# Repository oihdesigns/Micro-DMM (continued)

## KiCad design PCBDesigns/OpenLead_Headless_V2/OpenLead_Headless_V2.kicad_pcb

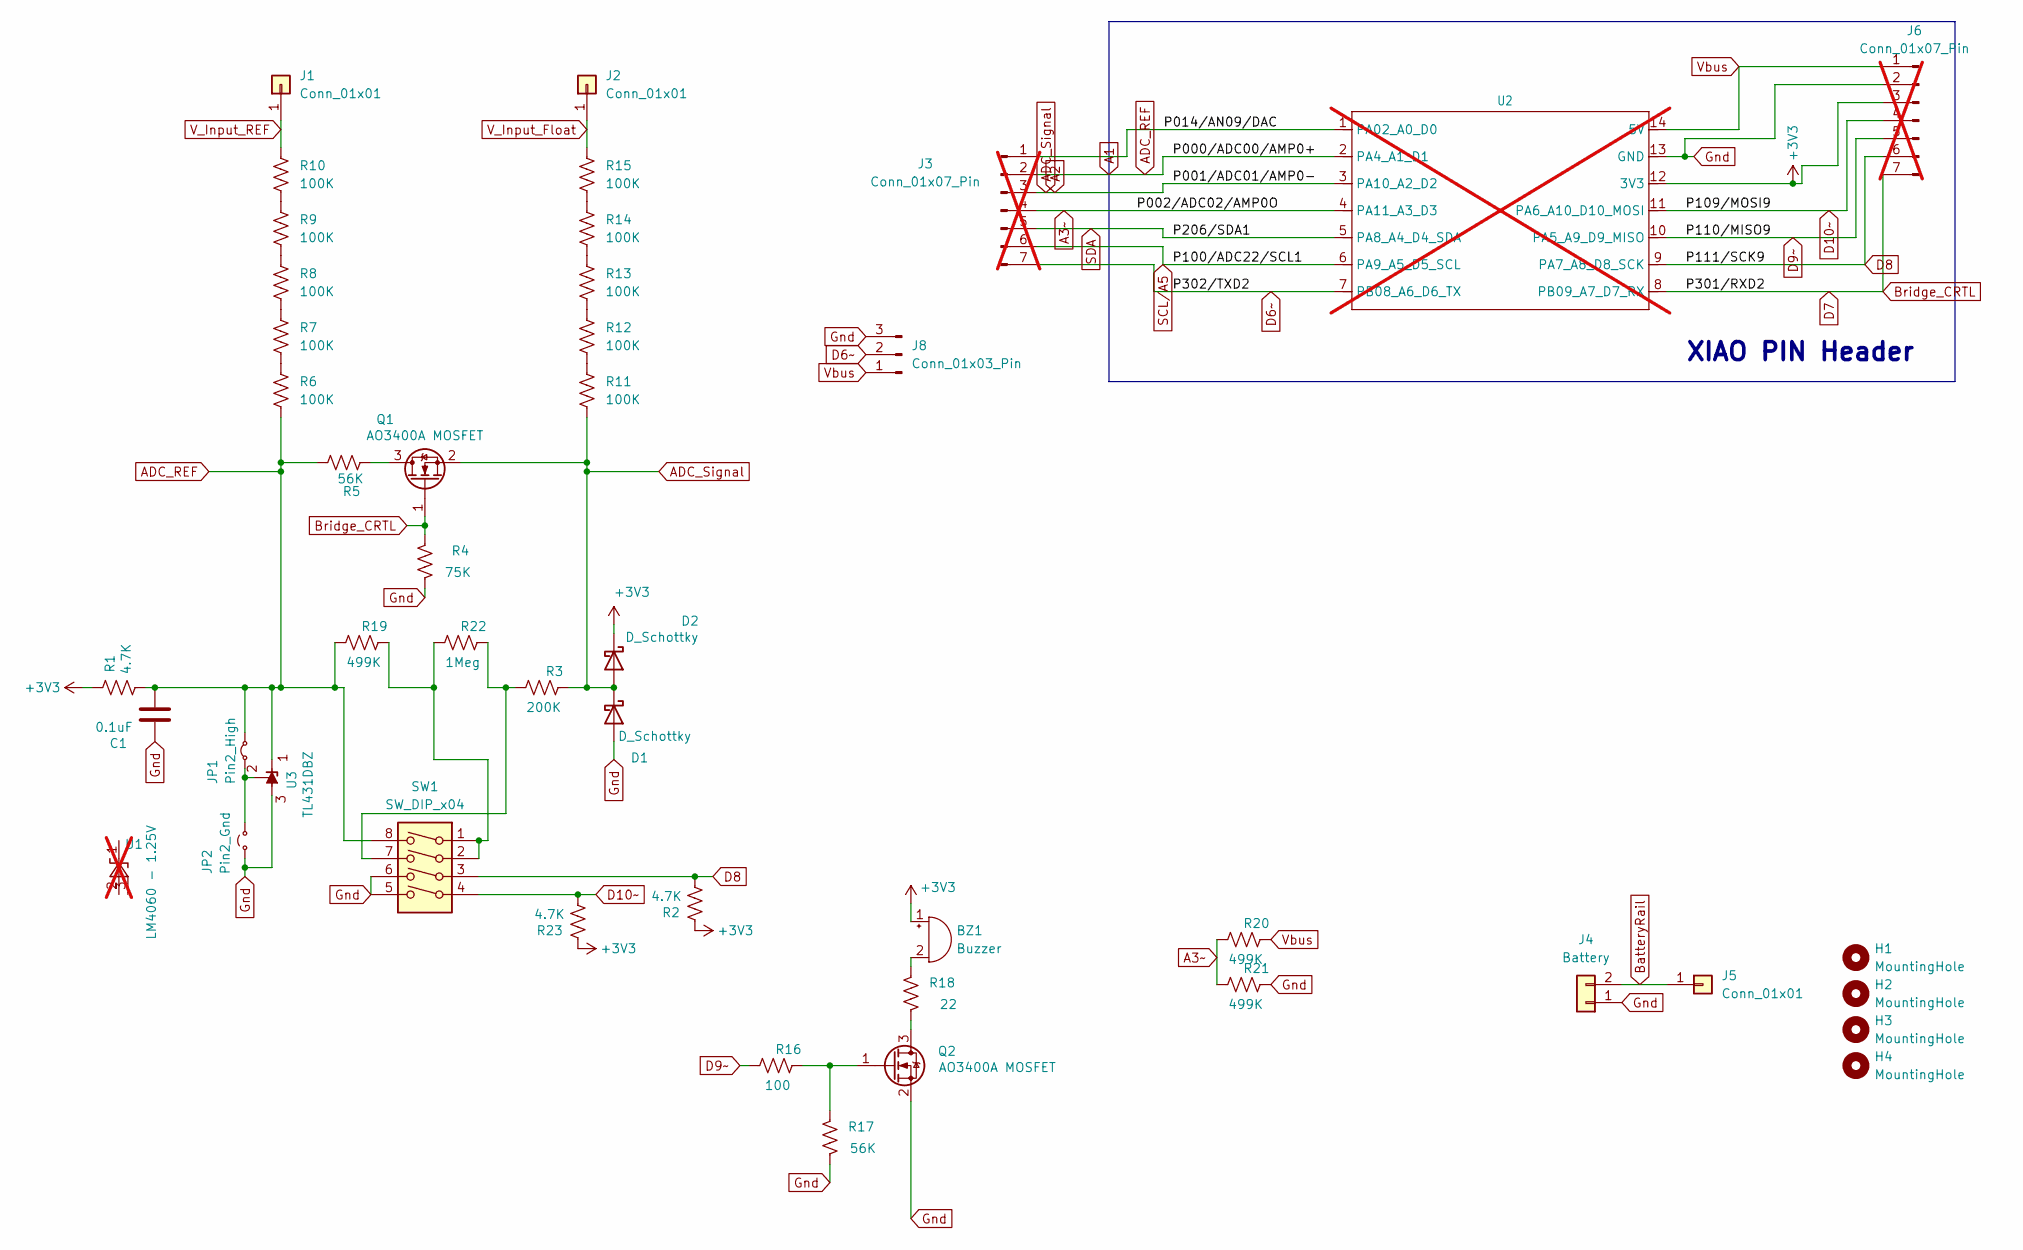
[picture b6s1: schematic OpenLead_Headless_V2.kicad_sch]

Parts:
BZ1: Buzzer; Buzzer_12x9.5RM7.6
C1: 0.1uF; C_0805_2012Metric
D1, D2: D_Schottky; D_SOD-123
H1, H2, H3, H4: MountingHole; MountingHole_2.2mm_M2_Pad
J1, J2: Conn_01x01; SolderWire-0.75sqmm_1x01_D1.25mm_OD2.3mm
J3, J6: Conn_01x07_Pin; PinSocket_1x07_P2.54mm_Vertical; not fitted
J4: Battery; PinHeader_1x02_P1.27mm_Vertical
J5: Conn_01x01; SolderWire-0.5sqmm_1x01_D0.9mm_OD2.1mm
J8: Conn_01x03_Pin; PinHeader_1x03_P1.27mm_Vertical
JP1: Pin2_High; SolderJumper-2_P1.3mm_Bridged_Pad1.0x1.5mm
JP2: Pin2_Gnd; SolderJumper-2_P1.3mm_Open_TrianglePad1.0x1.5mm
Q1, Q2: AO3400A MOSFET; SOT-23
R1, R2, R23: 4.7K; R_0805_2012Metric
R3: 200K; R_0805_2012Metric
R4: 75K; R_0805_2012Metric
R5, R17: 56K; R_0805_2012Metric
R6, R7, R8, R9, R10, R11, R12, R13, R14, R15: 100K; R_0805_2012Metric
R16: 100; R_0805_2012Metric
R18: 22; R_0805_2012Metric
R19, R20, R21: 499K; R_0805_2012Metric
R22: 1Meg; R_0805_2012Metric
SW1: SW_DIP_x04; SW_DIP_SPSTx04_Slide_KingTek_DSHP04TS_W7.62mm_P1.27mm
U1: LM4060 - 1.25V; SOT-23; not fitted
U2: not fitted
U3: TL431DBZ; SOT-23

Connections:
+3V3: BZ1.1 (+), D2.1 (K), J6.3, R1.1, R2.1, R23.1, U2.12 (3V3)
/P014/AN09/DAC: J3.1, U2.1 (PA02_A0_D0)
A1: C1.2, J3.2, JP1.2 (B), R1.2, R5.2, R6.2, R19.1, SW1.8, U2.2 (PA4_A1_D1), U3.1 (K)
A2: D1.1 (K), D2.2 (A), J3.3, Q1.2 (S), R3.2, R11.2, U2.3 (PA10_A2_D2)
A3~: J3.4, R20.1, R21.1, U2.4 (PA11_A3_D3)
BatteryRail: J4.2, J5.1 (Pin_1_1)
Bridge_CRTL: J6.7, Q1.1 (G), R4.2, U2.8 (PB09_A7_D7_RX)
D6~: J3.7, J8.2, U2.7 (PB08_A6_D6_TX)
D8: J6.6, R2.2, SW1.3, U2.9 (PA7_A8_D8_SCK)
D9~: J6.5, R16.1, U2.10 (PA5_A9_D9_MISO)
D10~: J6.4, R23.2, SW1.4, U2.11 (PA6_A10_D10_MOSI)
Gnd: C1.1, D1.2 (A), J4.1, J6.2, J8.3, JP2.1 (A), Q2.2 (S), R4.1, R17.1, R21.2, SW1.5, SW1.6, U2.13 (GND), U3.3 (A)
unnamed: BZ1.2 (-), R18.2
unnamed: JP1.1 (A), JP2.2 (B), U3.2 (REF)
unnamed: Q1.3 (D), R5.1
unnamed: Q2.3 (D), R18.1
unnamed: Q2.1 (G), R16.2, R17.2
unnamed: R6.1, R7.2
unnamed: R7.1, R8.2
unnamed: R8.1, R9.2
unnamed: R9.1, R10.2
unnamed: R11.1, R12.2
unnamed: R12.1, R13.2
unnamed: R13.1, R14.2
unnamed: R14.1, R15.2
unnamed: R19.2, R22.1, SW1.1, SW1.2
unnamed: R3.1, R22.2, SW1.7
SCL/A5: J3.6, U2.6 (PA9_A5_D5_SCL)
SDA: J3.5, U2.5 (PA8_A4_D4_SDA)
V_Input_Float: J2.1 (Pin_1_1), R15.1
V_Input_REF: J1.1 (Pin_1_1), R10.1
Vbus: J6.1, J8.1, R20.2, U2.14 (5V)

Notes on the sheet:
XIAO PIN Header

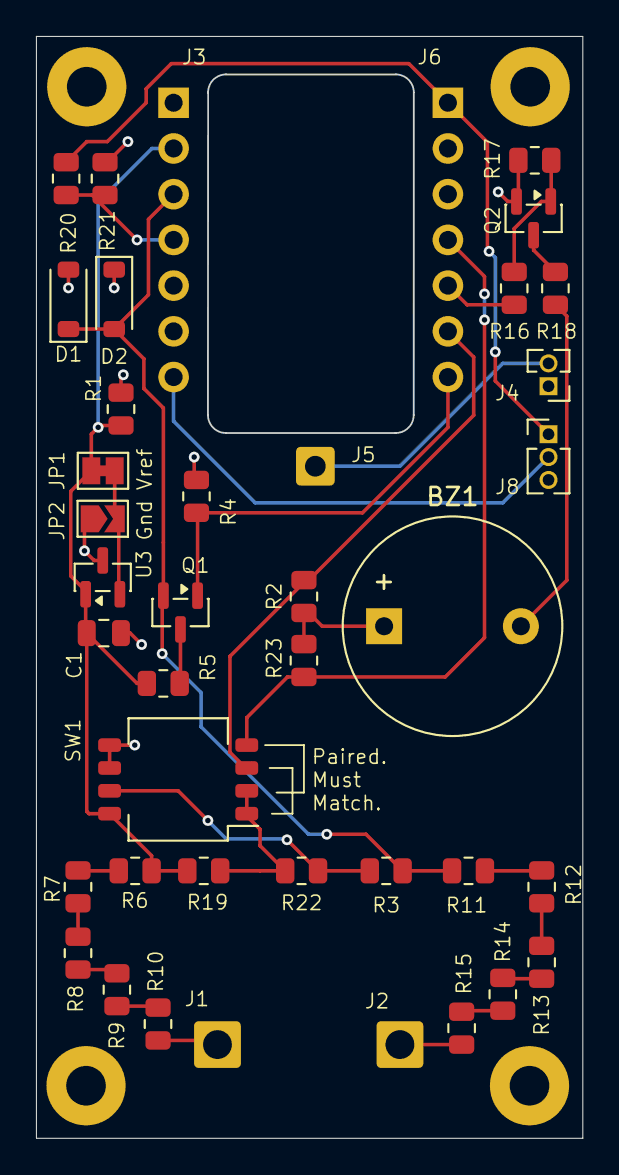
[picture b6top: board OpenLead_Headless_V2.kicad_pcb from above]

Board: 4 copper layers, 30.4 x 61.2 mm, 44 parts (0 on the bottom side), 29 nets.

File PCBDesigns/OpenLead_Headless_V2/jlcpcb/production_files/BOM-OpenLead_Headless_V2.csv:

Comment,Designator,Footprint,LCSC,Quantity
0.1uF,C1,C_0805_2012Metric,C28233,1
100,R16,R_0805_2012Metric,C17408,1
100K,"R10,R11,R12,R13,R14,R15,R6,R7,R8,R9",R_0805_2012Metric,C122537,10
1Meg,R22,R_0805_2012Metric,C445668,1
200K,R3,R_0805_2012Metric,C218415,1
22,R18,R_0805_2012Metric,C17561,1
4.7K,"R1,R2,R23",R_0805_2012Metric,C515732,3
499K,"R19,R20,R21",R_0805_2012Metric,C218596,3
56K,"R17,R5",R_0805_2012Metric,C218627,2
75K,R4,R_0805_2012Metric,C319485,1
AO3400A MOSFET,"Q1,Q2",SOT-23,C20917,2
D_Schottky,"D1,D2",D_SOD-123,C8598,2
SW_DIP_x04,SW1,SW_DIP_SPSTx04_Slide_KingTek_DSHP04TS_W7.62mm_P1.27mm,C3293144,1
TL431DBZ,U3,SOT-23,C8499,1
Conn_01x01,J1,SolderWire-0.75sqmm_1x01_D1.25mm_OD2.3mm,,1
Battery,J4,PinHeader_1x02_P1.27mm_Vertical,,1
Conn_01x01,J5,SolderWire-0.5sqmm_1x01_D0.9mm_OD2.1mm,,1
Conn_01x01,J2,SolderWire-0.75sqmm_1x01_D1.25mm_OD2.3mm,,1
Buzzer,BZ1,Buzzer_12x9.5RM7.6,,1
Conn_01x03_Pin,J8,PinHeader_1x03_P1.27mm_Vertical,,1
Pin2_Gnd,JP2,SolderJumper-2_P1.3mm_Open_TrianglePad1.0x1.5mm,,1
Pin2_High,JP1,SolderJumper-2_P1.3mm_Bridged_Pad1.0x1.5mm,,1

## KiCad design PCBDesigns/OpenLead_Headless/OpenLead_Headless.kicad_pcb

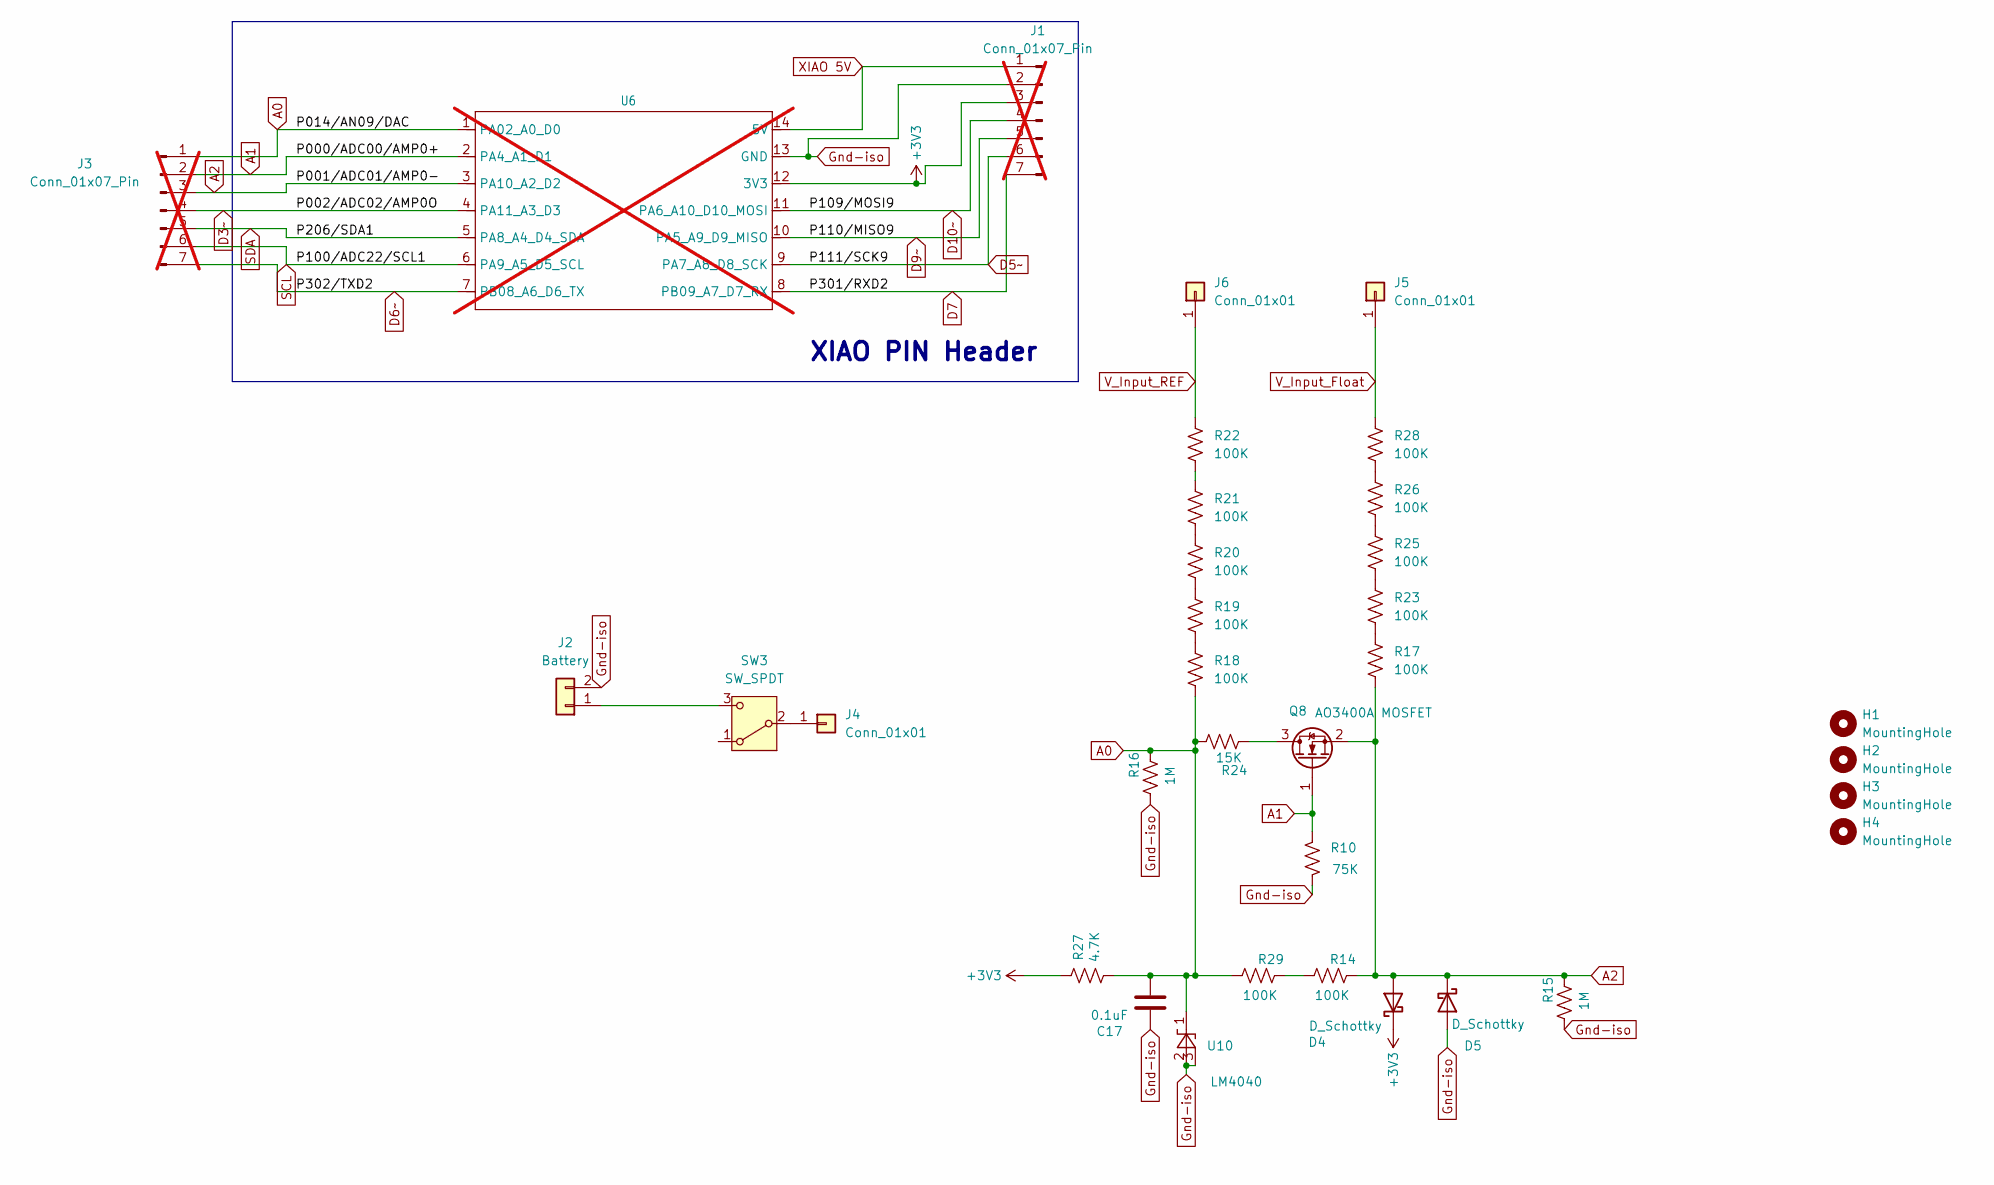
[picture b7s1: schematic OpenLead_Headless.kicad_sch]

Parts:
C17: 0.1uF; C_0805_2012Metric
D4, D5: D_Schottky; D_SOD-123
H1, H2, H3, H4: MountingHole; MountingHole_2.2mm_M2_Pad
J1, J3: Conn_01x07_Pin; PinSocket_1x07_P2.54mm_Vertical; not fitted
J2: Battery; PinSocket_1x02_P2.54mm_Vertical
J4: Conn_01x01; SolderWire-0.5sqmm_1x01_D0.9mm_OD2.1mm
J5, J6: Conn_01x01; SolderWire-0.75sqmm_1x01_D1.25mm_OD2.3mm
Q8: AO3400A MOSFET; SOT-23
R10: 75K; R_0805_2012Metric
R14, R17, R18, R19, R20, R21, R22, R23, R25, R26, R28, R29: 100K; R_0805_2012Metric
R15, R16: 1M; R_0805_2012Metric
R24: 15K; R_0805_2012Metric
R27: 4.7K; R_0805_2012Metric
SW3: SW_SPDT; SW_Slide_SPDT_Angled_CK_OS102011MA1Q
U6: not fitted
U10: LM4040; SOT-23

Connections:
+3V3: D4.1 (K), J1.3, R27.1, U6.12 (3V3)
A0: C17.2, J3.1, R16.2, R18.2, R24.2, R27.2, R29.1, U6.1 (PA02_A0_D0), U10.1 (K)
A1: J3.2, Q8.1 (G), R10.2, U6.2 (PA4_A1_D1)
A2: D4.2 (A), D5.1 (K), J3.3, Q8.2 (S), R14.2, R15.2, R17.2, U6.3 (PA10_A2_D2)
D3~: J3.4, U6.4 (PA11_A3_D3)
D5~: J1.6, U6.9 (PA7_A8_D8_SCK)
D6~: J3.7, U6.7 (PB08_A6_D6_TX)
D7: J1.7, U6.8 (PB09_A7_D7_RX)
D9~: J1.5, U6.10 (PA5_A9_D9_MISO)
D10~: J1.4, U6.11 (PA6_A10_D10_MOSI)
Gnd-iso: C17.1, D5.2 (A), J1.2, J2.2, R10.1, R15.1, R16.1, U6.13 (GND), U10.2 (A), U10.3 (nc_(gnd))
unnamed: J2.1, SW3.3 (C)
unnamed: J4.1 (Pin_1_1), SW3.2 (B)
unnamed: Q8.3 (D), R24.1
unnamed: R14.1, R29.2
unnamed: R17.1, R23.2
unnamed: R18.1, R19.2
unnamed: R19.1, R20.2
unnamed: R20.1, R21.2
unnamed: R21.1, R22.2
unnamed: R23.1, R25.2
unnamed: R25.1, R26.2
unnamed: R26.1, R28.2
SCL: J3.6, U6.6 (PA9_A5_D5_SCL)
SDA: J3.5, U6.5 (PA8_A4_D4_SDA)
V_Input_Float: J5.1 (Pin_1_1), R28.1
V_Input_REF: J6.1 (Pin_1_1), R22.1
XIAO 5V: J1.1, U6.14 (5V)

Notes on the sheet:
XIAO PIN Header

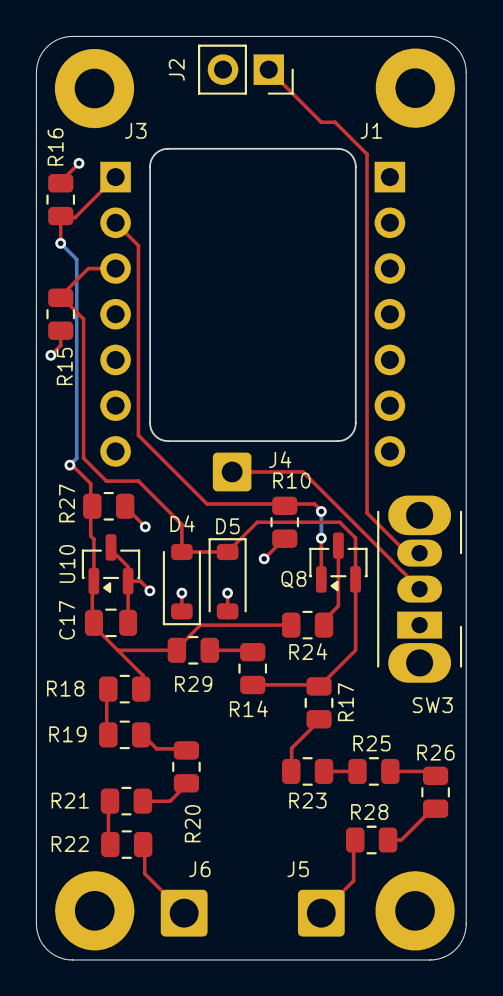
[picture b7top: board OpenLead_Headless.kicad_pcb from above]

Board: 4 copper layers, 23.9 x 51.3 mm, 33 parts (0 on the bottom side), 19 nets.

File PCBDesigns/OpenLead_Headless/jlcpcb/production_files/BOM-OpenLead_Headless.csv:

Comment,Designator,Footprint,LCSC,Quantity
0.1uF,C17,C_0805_2012Metric,C28233,1
100K,"R14,R17,R18,R19,R20,R21,R22,R23,R25,R26,R28,R29",R_0805_2012Metric,C122537,12
15K,R24,R_0805_2012Metric,C319846,1
1M,"R15,R16",R_0805_2012Metric,C218408,2
4.7K,R27,R_0805_2012Metric,C515732,1
75K,R10,R_0805_2012Metric,C319485,1
AO3400A MOSFET,Q8,SOT-23,C20917,1
D_Schottky,"D4,D5",D_SOD-123,C8598,2
LM4040,U10,SOT-23,C2156621,1
Conn_01x01,J4,SolderWire-0.5sqmm_1x01_D0.9mm_OD2.1mm,,1
Conn_01x01,J6,SolderWire-0.75sqmm_1x01_D1.25mm_OD2.3mm,,1
Conn_01x01,J5,SolderWire-0.75sqmm_1x01_D1.25mm_OD2.3mm,,1
Battery,J2,PinSocket_1x02_P2.54mm_Vertical,,1
SW_SPDT,SW3,SW_Slide_SPDT_Angled_CK_OS102011MA1Q,,1

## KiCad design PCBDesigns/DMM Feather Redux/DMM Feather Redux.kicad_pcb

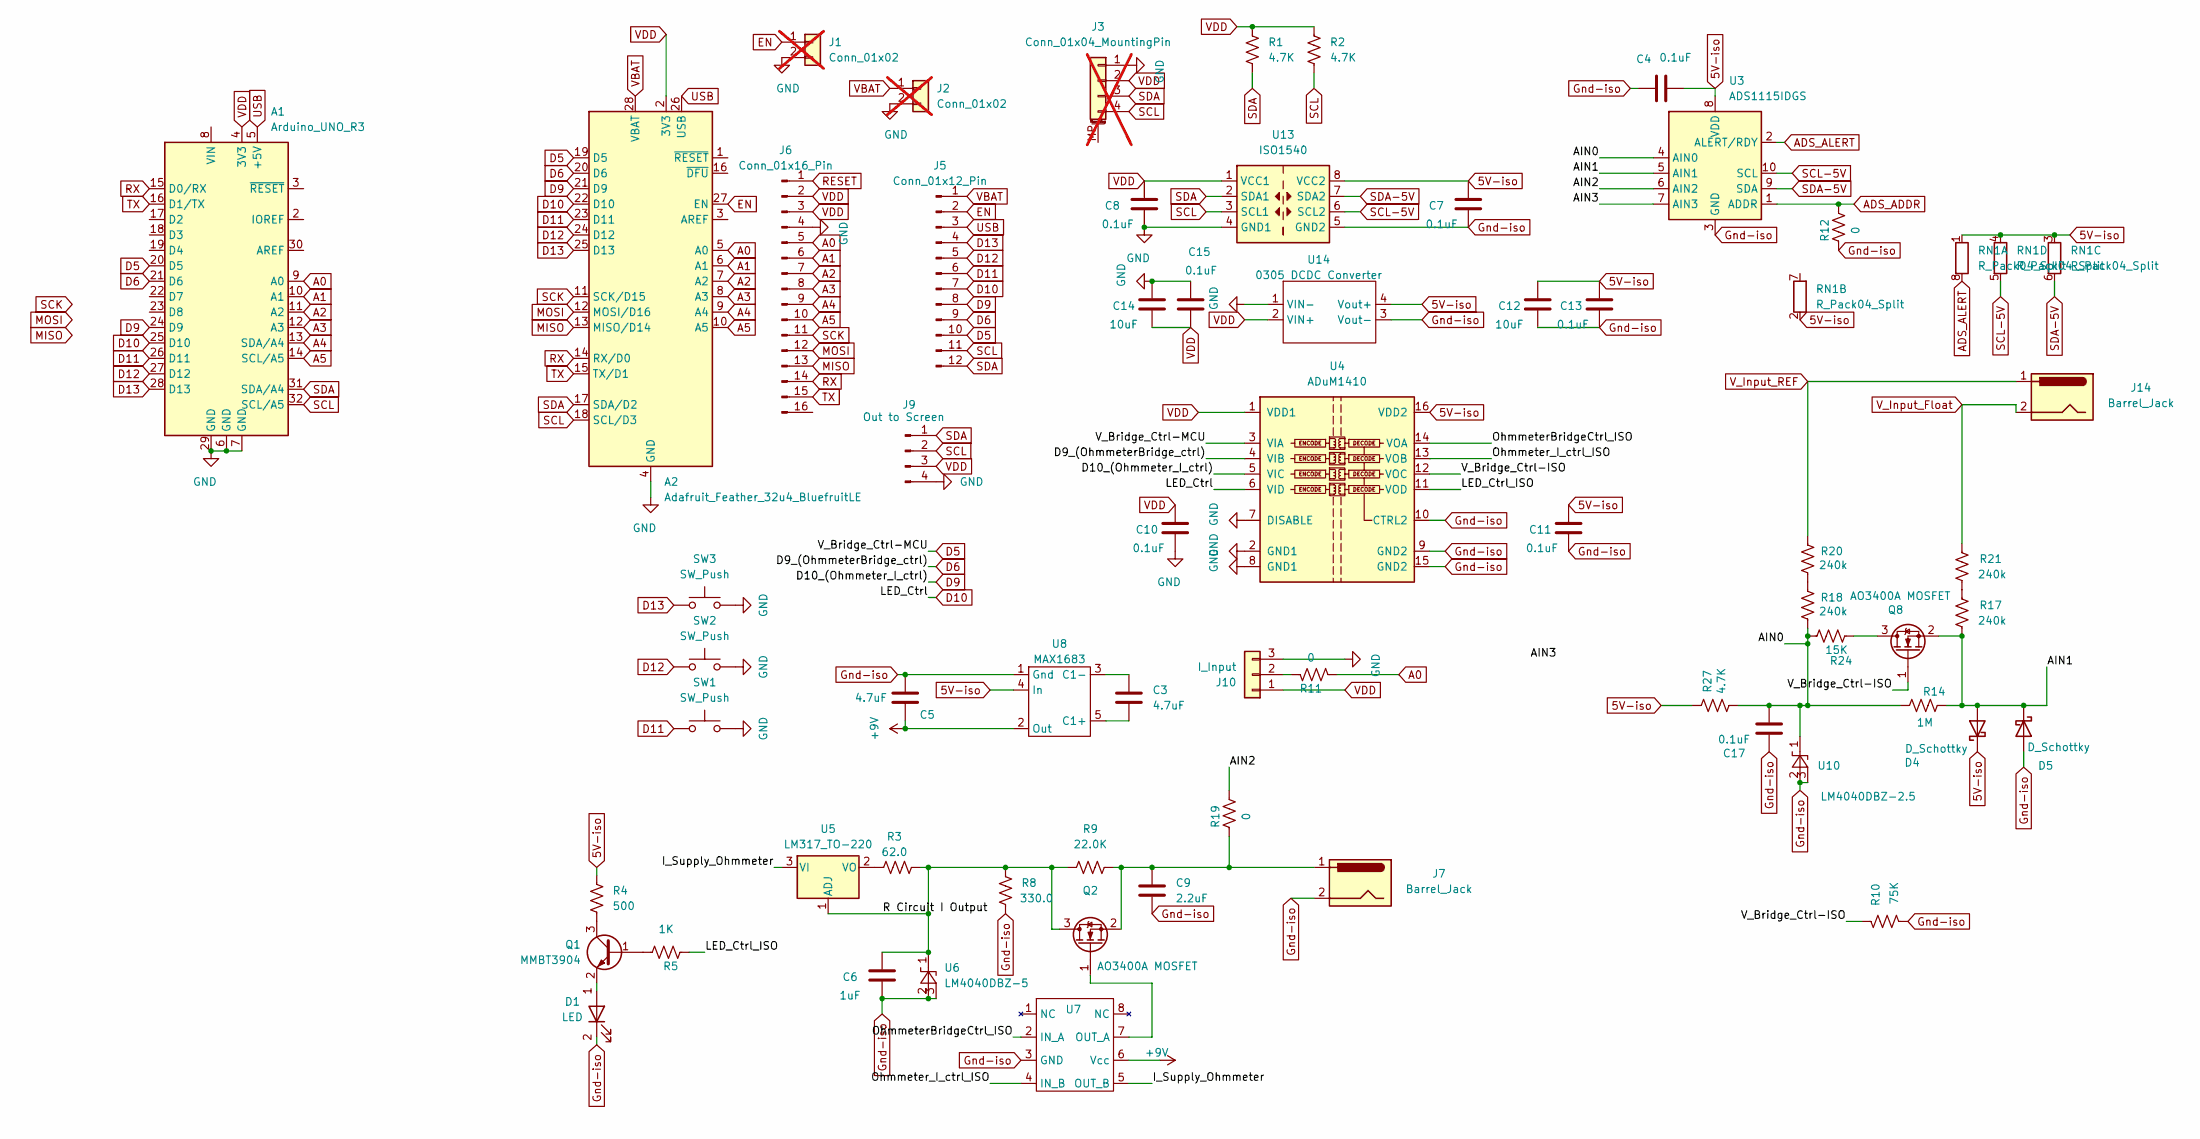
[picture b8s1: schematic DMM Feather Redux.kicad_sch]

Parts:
A1: Arduino_UNO_R3
A2: Adafruit_Feather_32u4_BluefruitLE; Adafruit_Feather_WithMountingHoles
C3, C5: 4.7uF; C_0805_2012Metric_Pad1.18x1.45mm_HandSolder
C4, C7, C8, C10, C11, C13, C15, C17: 0.1uF; C_0603_1608Metric
C6: 1uF; C_0805_2012Metric_Pad1.18x1.45mm_HandSolder
C9: 2.2uF; C_0805_2012Metric_Pad1.18x1.45mm_HandSolder
C12, C14: 10uF; C_0603_1608Metric
D1: LED; LED-SMD_L3.0-W3.0_WHITE
D4, D5: D_Schottky; D_SOD-123
J1, J2: Conn_01x02; PinSocket_1x02_P2.54mm_Vertical; not fitted
J3: Conn_01x04_MountingPin; JST_SH_SM04B-SRSS-TB_1x04-1MP_P1.00mm_Horizontal; not fitted
J5: Conn_01x12_Pin; PinSocket_1x12_P2.54mm_Vertical
J6: Conn_01x16_Pin; PinSocket_1x16_P2.54mm_Vertical
J7, J14: Barrel_Jack; BarrelJack_Horizontal
J9: Out to Screen; PinSocket_1x04_P2.54mm_Vertical
J10: I_Input; PinSocket_1x03_P2.54mm_Vertical
Q1: MMBT3904; SOT-23
Q2, Q8: AO3400A MOSFET; SOT-23
R1, R2, R27: 4.7K; R_0603_1608Metric
R3: 62.0; R_0805_2012Metric
R4: 500; R_0805_2012Metric
R5: 1K; R_0603_1608Metric
R8: 330.0; R_0805_2012Metric
R9: 22.0K; R_0805_2012Metric
R10: 75K; R_0603_1608Metric
R11, R12, R19: 0; R_0603_1608Metric
R14: 1M; R_0805_2012Metric
R17, R18, R20, R21: 240k; R_0805_2012Metric
R24: 15K; R_0805_2012Metric
RN1: R_Pack04_Split; R_Array_Convex_4x0603
SW1, SW2, SW3: SW_Push; SW_Push_1P1T-SH_NO_CK_KMR2xxG
U3: ADS1115IDGS; TSSOP-10_3x3mm_P0.5mm
U4: ADuM1410; SOIC-16W_7.5x10.3mm_P1.27mm
U5: LM317_TO-220; SOT-223-3_TabPin2
U6: LM4040DBZ-5; SOT-23
U7: IX4426N; SOIC-8_3.9x4.9mm_P1.27mm
U8: MAX1683; SOT-23-5_HandSoldering
U10: LM4040DBZ-2.5; SOT-23
U13: ISO1540; SOIC-8_3.9x4.9mm_P1.27mm
U14: 0305 DCDC Converter; XP SCT01F03S05

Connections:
5V-iso: C4.2, C7.1, C11.1, C12.1, C13.1, D4.1 (K), R4.2, R27.1, RN1.1 (R1.1), RN1.2 (R2.1), RN1.3 (R3.1), RN1.4 (R4.1), U3.8 (VDD), U4.16 (VDD2), U8.4 (In), U13.8 (VCC2), U14.4 (Vout+)
+9V: C5.2, U7.6 (Vcc), U8.2 (Out)
/AIN0: C17.2, R14.1, R18.2, R24.2, R27.2, U3.4 (AIN0), U10.1 (K)
/AIN1: D4.2 (A), D5.1 (K), Q8.2 (S), R14.2, R17.2, U3.5 (AIN1)
/AIN2: R19.1, U3.6 (AIN2)
/AIN3: U3.7 (AIN3)
/I_Supply_Ohmmeter: U5.3 (VI), U7.5 (OUT_B)
/LED_Ctrl_ISO: R5.1, U4.11 (VOD)
/OhmmeterBridgeCtrl_ISO: U4.14 (VOA), U7.2 (IN_A)
/Ohmmeter_I_ctrl_ISO: U4.13 (VOB), U7.4 (IN_B)
/R Circuit I Output: C6.1, Q2.3 (D), R3.2, R8.2, R9.1, U5.1 (ADJ), U6.1 (K)
/V_Bridge_Ctrl-ISO: Q8.1 (G), R10.2, U4.12 (VOC)
A0: A1.9 (A0), A2.5 (A0), J6.5, R11.1
A1: A1.10 (A1), A2.6 (A1), J6.6
A2: A1.11 (A2), A2.7 (A2), J6.7
A3: A1.12 (A3), A2.8 (A3), J6.8
A4: A1.13 (SDA/A4), A2.9 (A4), J6.9
A5: A1.14 (SCL/A5), A2.10 (A5), J6.10
ADS_ADDR: R12.1, U3.1 (ADDR)
ADS_ALERT: RN1.8 (R1.2), U3.2 (ALERT/RDY)
D5: A1.20 (D5), A2.19 (D5), J5.10, U4.3 (VIA)
D6: A1.21 (D6), A2.20 (D6), J5.9, U4.4 (VIB)
D9: A1.24 (D9), A2.21 (D9), J5.8, U4.5 (VIC)
D10: A1.25 (D10), A2.22 (D10), J5.7, U4.6 (VID)
D11: A1.26 (D11), A2.23 (D11), J5.6, SW1.1
D12: A1.27 (D12), A2.24 (D12), J5.5, SW2.1
D13: A1.28 (D13), A2.25 (D13), J5.4, SW3.1
EN: A2.27 (EN), J1.1, J5.2
GND: A1.6 (GND), A1.7 (GND), A1.29 (GND), A2.4 (GND), C8.2, C10.2, C14.1, C15.1, J1.2, J2.2, J3.1, J6.4, J9.4, J10.3, SW1.2, SW2.2, SW3.2, U4.2 (GND1), U4.7 (DISABLE), U4.8 (GND1), U13.4 (GND1), U14.1 (VIN-)
Gnd-iso: C4.1, C5.1, C6.2, C7.2, C9.2, C11.2, C12.2, C13.2, C17.1, D1.2 (K), D5.2 (A), J7.2, R8.1, R10.1, R12.2, U3.3 (GND), U4.9 (GND2), U4.10 (CTRL2), U4.15 (GND2), U6.2 (A), U6.3 (nc_(gnd)), U7.3 (GND), U8.1 (Gnd), U10.2 (A), U10.3 (nc_(gnd)), U13.5 (GND2), U14.3 (Vout-)
MISO: A2.13 (MISO/D14), J6.13
MOSI: A2.12 (MOSI/D16), J6.12
unnamed: D1.1 (A), Q1.2 (E)
unnamed: J10.2, R11.2
unnamed: Q1.1 (B), R5.2
unnamed: Q1.3 (C), R4.1
unnamed: Q2.1 (G), U7.7 (OUT_A)
unnamed: C9.1, J7.1, Q2.2 (S), R9.2, R19.2
unnamed: Q8.3 (D), R24.1
unnamed: R17.1, R21.2
unnamed: R18.1, R20.2
unnamed: R3.1, U5.2 (VO)
unnamed: C3.2, U8.5 (C1+)
unnamed: C3.1, U8.3 (C1-)
RESET: J6.1
RX: A1.15 (D0/RX), A2.14 (RX/D0), J6.14
SCK: A2.11 (SCK/D15), J6.11
SCL: A1.32 (SCL/A5), A2.18 (SCL/D3), J3.4, J5.11, J9.2, R2.2, U13.3 (SCL1)
SCL-5V: RN1.5 (R4.2), U3.10 (SCL), U13.6 (SCL2)
SDA: A1.31 (SDA/A4), A2.17 (SDA/D2), J3.3, J5.12, J9.1, R1.2, U13.2 (SDA1)
SDA-5V: RN1.6 (R3.2), U3.9 (SDA), U13.7 (SDA2)
TX: A1.16 (D1/TX), A2.15 (TX/D1), J6.15
USB: A1.5 (+5V), A2.26 (USB), J5.3
VBAT: A2.28 (VBAT), J2.1, J5.1
VDD: A1.4 (3V3), A2.2 (3V3), C8.1, C10.1, C14.2, C15.2, J3.2, J6.2, J6.3, J9.3, J10.1, R1.1, R2.1, U4.1 (VDD1), U13.1 (VCC1), U14.2 (VIN+)
V_Input_Float: J14.2, R21.1
V_Input_REF: J14.1, R20.1

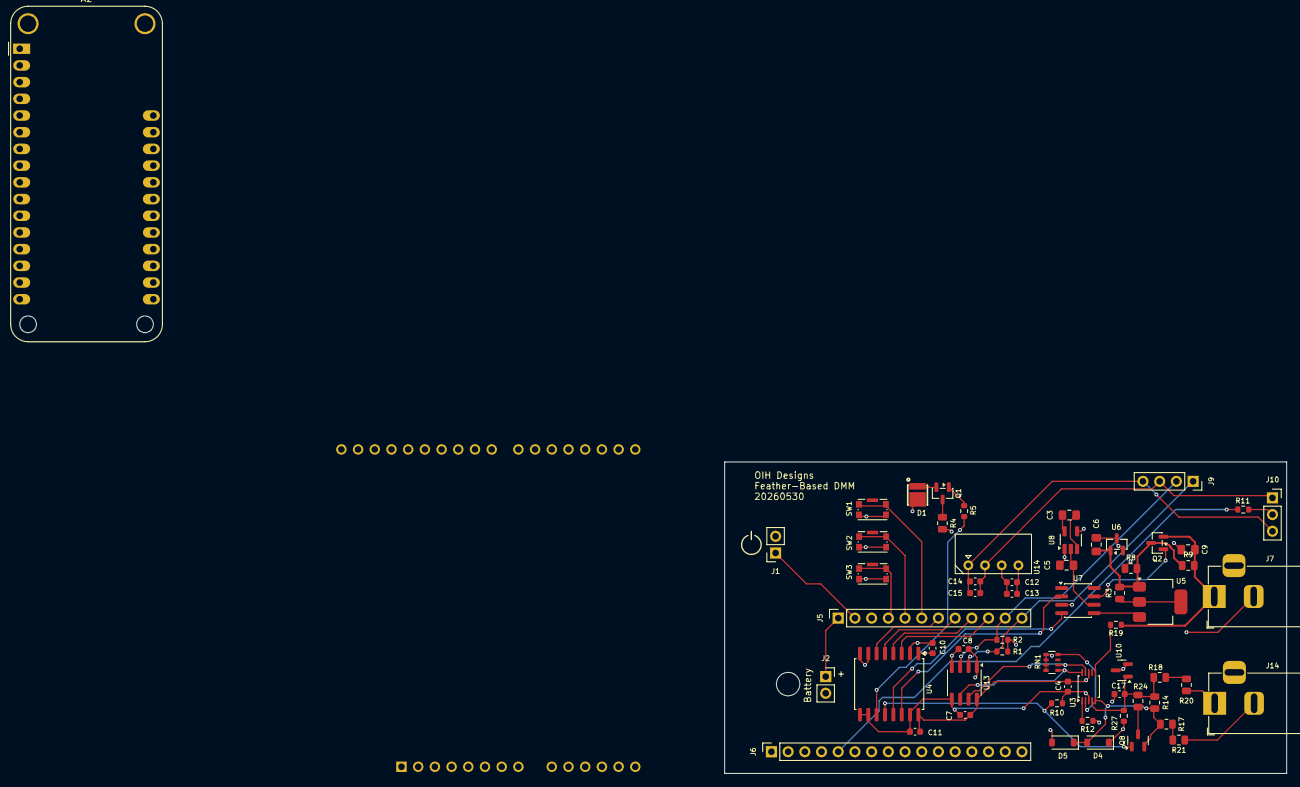
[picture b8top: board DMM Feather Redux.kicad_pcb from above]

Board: 4 copper layers, 85.5 x 47.4 mm, 61 parts (1 on the bottom side), 55 nets.

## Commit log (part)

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2025-06-22 Current Version as of Github Setup
    Something of an Advanced Beta
2025-06-22 Current User Manual
    Initial Git Upload
2025-06-22 Initial Serial Terminal Upload
2025-06-22 Collected Spreadsheets
    BOM, Measurement Math, and Calibrations.
2025-06-22 KiCad Design Files
    Initial Git Upload
2025-06-22 Renaming the main file test
2025-06-22 Broke EEPROM Cals out to their own tab
2025-06-22 Adjusted Resistor Null Offset and Digit Display
2025-06-22 Adding LTSpice Models of the Analog Ciruits
2025-06-22 LTSpice files into their own folder
2025-06-23 Added a "Hold Value" display option
    Now you can hold a value with the "type" button. It only types the value when you're in "type" mode.
2025-06-23 Added a "High Resistance" Mode
    This is a mode for measurements over 1M Ohms. Some of the auto power save / screen comfort settings assume the circuit is open at a threshold set below the theoretical max to avoid noise triggers. Th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
2025-06-25 Cleaning Aux Files
2025-06-25 Adding some photos
2025-06-25 Updated current reading code.
    Updated formatting of current reading mode for better auto-ranging.
2025-06-25 Creating an ESP32 Version
    In progress
2025-06-26 ESP32 EEPROM corrections.
2025-06-26 Added Manual VAC Mode
2025-06-27 Working on a Giga-COmpatible DMM code.
    Also working on adding level shifting to the next PCB design.
2025-06-27 Preserved a Giga version that works on the default (I2C) screen
    Might be useful for testing
2025-06-27 More updates to the next PCB
2025-06-28 More work on the Giga Version
2025-06-28 Working on Giga Files
    And seeing if I can make it work with an ADS1256 for more bits.
2025-06-29 Added Touchscreen Buttons to the Giga Shield Version
    Revised next PCB for power input options
2025-06-29 Added Voltage Plot
2025-06-29 More Button Refinement
2025-06-29 Button Refinement for the Giga Touchscreen
2025-06-30 Further Giga Refinements
2025-07-01 Developing RP2350 Implemetation
2025-07-02 File rearrangement
2025-07-02 Adding USB thumbdrive data logging for Giga
2025-07-04 Better Giga Autolog Implementation
2025-07-04 Starting to make an ADS1256 Version
    And minor XAIO RA4M1 edits
2025-07-04 Giga Auto Data Logging Refinements
2025-07-05 Display Improvements for the Giga Shield
2025-07-05 Couple further refinements
2025-07-05 General Giga Function Improvements
    Using the built-in LED now. Option to plot the resistance readings. Reverting to previous more general version of calibration values.
2025-07-05 Groundwork for simultaneous V&I plots.
2025-07-06 Minor Giga Screen Refinements
2025-07-07 Calibrating the Giga Version
    1256 Version remains completely non functional
2025-07-10 Minor Giga Improvements / File Rearrangement
2025-07-11 Removed DAC, not ready yet. Added loop monitor pin
2025-07-12 Working On Implementing Continuity in the Voltmeter
2025-07-13 The Giga version now can tell between floating or open in voltmeter mode
2025-07-14 Added feature for Giga version to report if 0vdc is due to open leads or same net.
2025-07-14 Moving to the KiCAD 9
2025-07-15 Giga version now shows int reading for float/closed determination.
2025-07-16 Minor float or closed (VAC trigger) adjustment
2025-07-17 Giga Version Refinements, Added white paper on the auto floating probes detect voltmeter design
2025-07-17 Updates to paper following updates
2025-07-19 Minor Edits to Paper
2025-07-22 Implementing function generator/audio alerts over the DACs using second core
2025-07-23 Changed name of paper, minor Giga edits
2025-07-23 Removed previous paper
2025-07-24 Updated RA4M1 Arduino sketch for open-lead sensing
2025-07-26 Revised the audio alerts
2025-07-27 Working on adding headphone control
2025-07-27 Further Refinement of headphones / microphone audio interface
2025-07-31 Mostly working on the next PCB
2025-08-01 Minor PCB Updates
2025-08-02 PCB work
2025-08-04 KiCAD Updates
2025-08-07 Working on things
2025-08-10 Making a Version of Code for Newest PCB Revision
2025-08-10 Update microDMM_RA4M1_XIAO_SMD_V5.ino
    Further adjustments to the program for the new board version.
2025-08-11 Updates to the programming files for the V5 boards
2025-08-12 Minor Giga Updates, Working on a business card size version
2025-08-13 Working on next PCB, mostly.
2025-08-13 Fixed ammeter problem and some nuisance alerts on Giga version
2025-08-14 Edits to the RA4M1 version and KiCAD work
2025-08-15 Minor KiCAD updates and file reorganization
2025-08-17 Arduino Code Updates for a PCB change
2025-08-20 Misc Arduino Files Work
2025-08-24 Working on the next PCBs
2025-08-30 Adjusting the open volt detection and power save logics.
2025-08-30 Debugging XAIO version sleep mode
2025-08-30 Work on next PCB version
2025-09-06 Working on PCBs and Separating Out Different Versions
2025-09-27 Add Raspberry Pi Tkinter UI and logging workflow
2025-09-27 Add Raspberry Pi hardware abstraction and control audit
2025-09-27 Add ADS1256 backend with auto-ranging measurement helpers
2025-09-27 Gathering RPI Port Files
2025-09-27 Add Raspberry Pi runtime harness and setup docs
2025-09-27 Allow running run_pi.py as a standalone script
2025-09-27 Add debug UI harness with configurable channels and GPIO controls
2025-09-27 Minor PCB Revisions
2025-09-27 Fix standalone execution for debug harness
2025-09-27 Add debug measurement mode with runtime clock
2025-09-27 Fix debug voltage display
2025-09-28 Add debug controls for gain, sample rate, and calibration
2025-09-28 Handle missing sample rate attribute in debug view
2025-09-28 Make debug controls panel visible by default
2025-09-28 Make debug controls permanently visible
2025-09-28 Expose ADC controls in Pi UI
2025-09-28 Move ADC controls into dedicated tab
2025-09-29 Moving Files Around
2025-09-30 Working on an FT232H (direct computer interface) version.
2025-10-02 FT232 Chip Updates
2025-10-02 Add FT232H desktop micro-DMM application
2025-10-02 Fix NameError when updating continuity output
2025-10-03 Add advanced ADS1115 controls and restore continuity blink
2025-10-03 Speed up continuity output and add manual pin overrides
2025-10-04 Refine FT232H defaults and bridge voltage visibility
2025-10-04 Add GUI control to clear VAC accumulator
2025-10-04 Restructure GUI layout and add burst logging capture
2025-10-04 Fix RMS buffer to store squared samples
2025-10-04 Stabilize VAC RMS calculation and surface Blinka import errors
2025-10-05 Working on the R Pi version
2025-10-05 Add integrated ADS1256 GUI with DMM math and trigger options
2025-10-05 Fix ADS1256 capture flow and add live view controls
2025-10-05 Restore ADC readings and split live controls
2025-10-11 Add advanced trigger positioning modes
2025-10-11 Calibrate ADS1256 after gain or rate changes
2025-10-12 Updating Program
2025-10-12 Update ADS1256 GUI V3_triggering.py
    Working on calibrations
2025-10-19 Giga Open Lead Detection Revisions & Minor PCB edits
2025-10-22 Expanding the Nano Differential Voltmeter
2025-10-23 Further updates
2025-10-25 Working on a revised instrumentation-focused PCB
2025-10-25 Voltmeter Front End Conditioning PCB
2025-10-25 Learning QSpice
2025-10-26 Finishing PCBs to be made.
2025-11-02 More work on an simulated process controller
2025-11-02 More process controller prototyping
2025-11-08 Working on the open lead detect process controller
2025-11-08 Further process meter w/ open lead detect work
2025-11-09 More Open Lead Process Meter Development
2025-11-09 Additional process meter refinements
2025-11-09 More tests and refinements of the process meter
2025-11-10 Various Minor Changes
2025-11-12 Revised open vs closed reporting to be second order instead of first
2025-11-12 Added a potentiometer for on the fly adjustment of the open lead threshold
2025-11-17 Work on voltmeter open lead detect demo
2025-11-27 New AdaLogger Version and PCB revisions
2025-11-27 Adafruit Datalogger work (works now) and other
2025-11-28 Adding a second channel to the datalogger
2025-11-30 Work on the RP2040 logger and Open Lead Detect Meter
2025-11-30 Modified logger with adjustable trigger threshold.
2025-12-06 AdaLogger behavior improvements
    - Only one log file for both interval and triggered writes.
    - Logs are stamped with relative time since previous write in uS.
    - New auto data plotter version
2025-12-12 Cleanup of PCB files
2025-12-12 Working on Uno Form specific DMM
2025-12-12 Finished(?) an Uno footprint board, started on Feather specific
2025-12-18 Some V2 Isolator PCB work and some radio data tests
2025-12-20 Updating the datalogger to support an RTC module
2025-12-21 Adding an autoranging feature to the Adalogger voltmeter
2025-12-21 Revise ReadMe with updates on switches and battery
    Updated DIP switch description and added operating notes for shutting down the board. Revised battery monitoring section to clarify voltage display and added notes on log file creation and known limi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
2025-12-21 Added both a temp sensor and the "mark place" button for the log
2025-12-26 Some radio work. Adding circuit disable to open lead detect proof.
2025-12-27 Upgraded the Open-Lead Detect Circuit so bias voltage it can be turned on and off.
    This gives the option of either having the open lead detect, or a wider range without the upbiasing circuitry that puts a small signal into the device being probed.
2025-12-27 Working on next voltmeter PCB
2025-12-30 Programming Changes
    - More serial info in the Adalogger
    - Split Open Lead Detect Proof into the known-working MOSFET version, and a prototype not-working photo-MOSFET version.
    - Working on next Isolated ADS1X15 PCB
2026-01-05 Finishing a V2 of the ADS Isolated board. Radio Comm Board Program.
2026-01-11 Data Capture for Open Lead Detect, Swap Differential on AdaLogger
2026-01-17 Made a new logger version that can now do current and voltage simultaneously.
2026-01-18 Logger code and isolated voltmeter PCB adjustments
2026-01-19 Data Logger Version Now with Acceleration
2026-01-20 Updates for accel log threshold
2026-01-21 Minor programming updates
2026-02-01 Moved various files around for cleanup. Made Claude version of logger with improvements (beta)
2026-02-02 Made a new version of the Open Lead Detect Voltmeter that runs on an ESP32-S3 (with tft display)
2026-02-06 Added avg calc and optimized some parameters.
2026-02-07 Many improvements, including support for either an ADS1115 or ADS1015
2026-02-12 Various simple DMM / Scope work (including headless version)
2026-02-13 Improvements to the headless sketch and GUI
2026-02-16 Updated programs and worked on PCB designs...
2026-02-17 Added smoothing to generic voltmeter, and worked on AMC0330R PCB
2026-02-23 Various troubleshooting and PCB design
2026-02-26 Made a datalogger Android app and moved some datalogging files around
2026-03-07 Syncing Android Apps and various minor updates
2026-03-22 Made a datalogger version with larger TFT screen.
2026-04-19 Updates, see description
    Updated programming for open lead detect board
    worked on various PCBs, including a new open lead voltmeter design with few components
2026-04-19 Programmed a test board for some isolated readings
2026-04-20 Added in-progress CAN AMC test board
2026-05-25 Work on different PCBs. Mostly.
2026-05-25 More PCB work.
2026-05-29 PCB Work.
2026-05-31 DMM PCB work and Voltmeter Sketch Updates
2026-05-31 Circuits, mostly
2026-06-05 Giga Controller Updates
2026-06-05 More Giga GUI updates
2026-06-06 Giga GUI Improvements
2026-06-07 Many Giga GUI updates
2026-06-09 Many Giga Remote updates
2026-06-17 Misc project work over the last few days.
    LTSpice diff buffer design, some logger work, capturing data on my open-lead-detect circuit, designing a new open lead detect PCB.
2026-06-18 Open Lead Voltmeter now shows approx resistance
2026-06-20 Data Collection and minor revisions for Open Lead DMM
2026-06-21 More Open Lead Detect Diagnostic Work
2026-06-22 Lots of data collection, with some code updates on timings and thresholds.
2026-06-23 Further data collection and minor program edits.
2026-06-24 Minimal Open Lead Detect has a simpler board selection method.
